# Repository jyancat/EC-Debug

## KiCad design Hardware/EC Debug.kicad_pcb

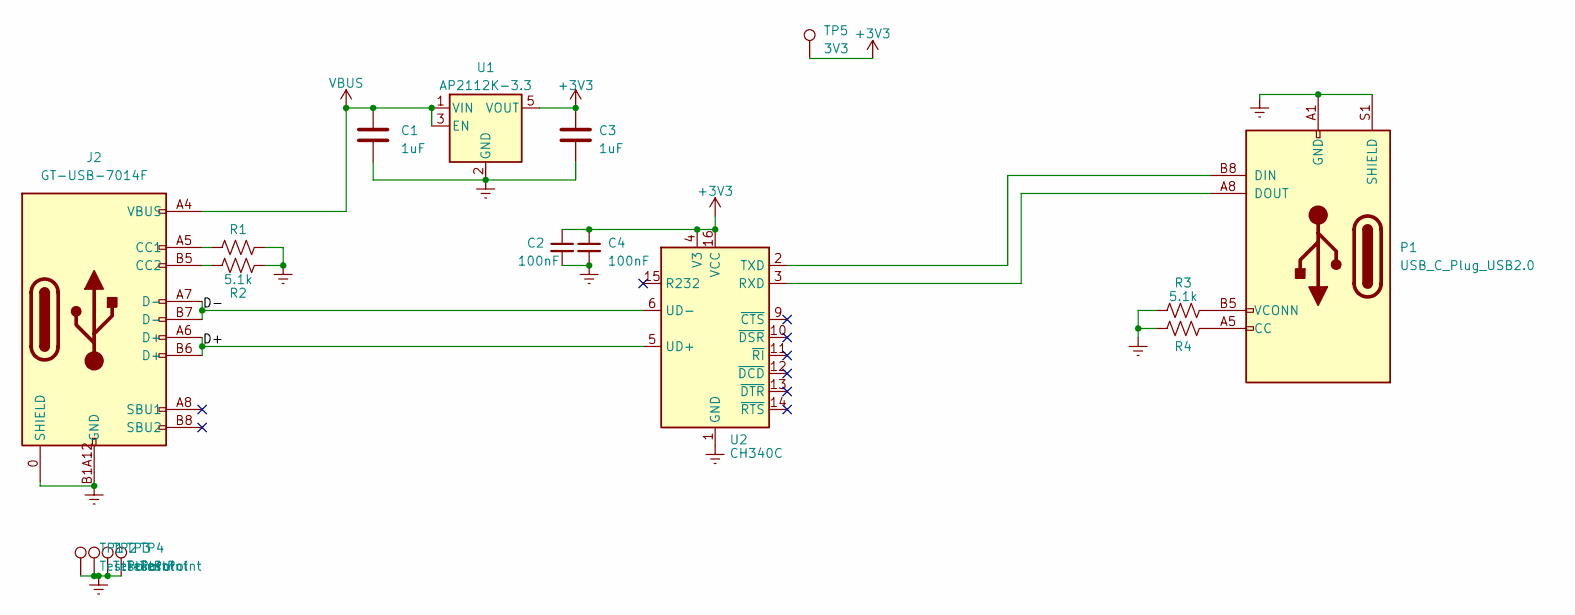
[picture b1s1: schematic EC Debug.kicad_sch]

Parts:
C1, C3: 1uF; C_0402_1005Metric
C2, C4: 100nF; C_0402_1005Metric
J2: GT-USB-7014F; LCSC Part C3001282
P1: USB_C_Plug_USB2.0; 105444
R1, R2, R3, R4: 5.1k; R_0402_1005Metric
TP1, TP2, TP3, TP4: TestPoint; TestPoint_Pad_1.5x1.5mm
TP5: 3V3; TestPoint_Pad_D1.0mm
U1: AP2112K-3.3; SOT-23-5
U2: CH340C; SOIC-16_3.9x9.9mm_P1.27mm

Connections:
+3V3: C2.1, C3.1, C4.1, TP5.1, U1.5 (VOUT), U2.4 (V3), U2.16 (VCC)
/D+: J2.A6 (D+), J2.B6 (D+), U2.5 (UD+)
/D-: J2.A7 (D-), J2.B7 (D-), U2.6 (UD-)
Earth: C1.2, C2.2, C3.2, C4.2, J2.0 (SHIELD), J2.A1B12 (GND), J2.B1A12 (GND), P1.A1 (GND), P1.A12 (GND), P1.B1 (GND), P1.B12 (GND), P1.S1 (SHIELD), R1.1, R2.1, R3.1, R4.1, TP1.1, TP2.1, TP3.1, TP4.1, U1.2 (GND), U2.1 (GND)
unnamed: J2.A5 (CC1), R1.2
unnamed: J2.B5 (CC2), R2.2
unnamed: P1.A5 (CC), R4.2
unnamed: P1.B8 (DIN), U2.2 (TXD)
unnamed: P1.A8 (DOUT), U2.3 (RXD)
unnamed: P1.B5 (VCONN), R3.2
VBUS: C1.1, J2.A4 (VBUS), J2.B4 (VBUS), U1.1 (VIN), U1.3 (EN)

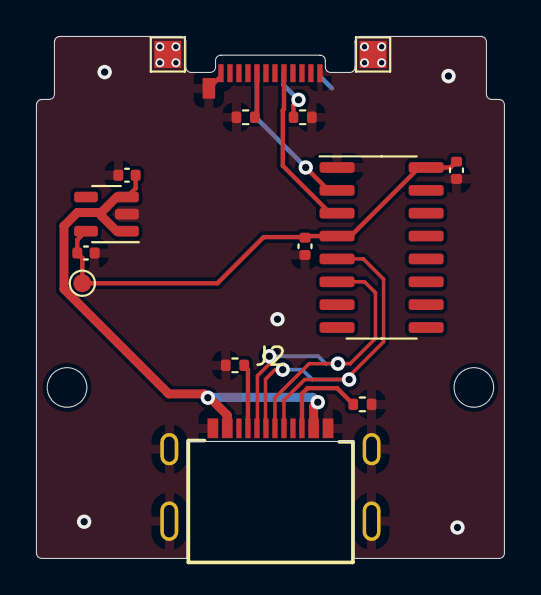
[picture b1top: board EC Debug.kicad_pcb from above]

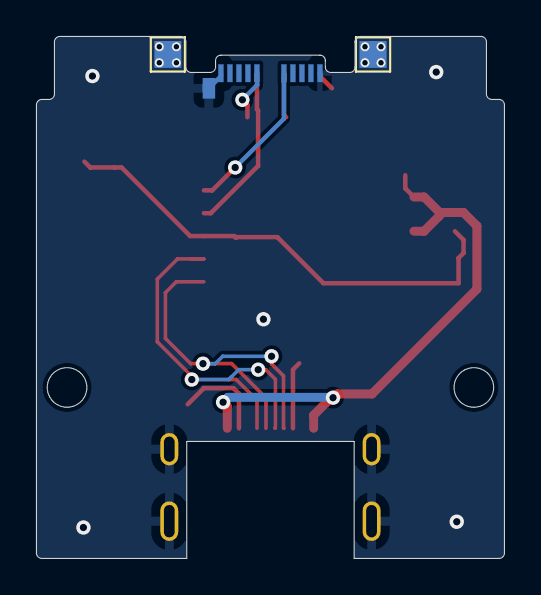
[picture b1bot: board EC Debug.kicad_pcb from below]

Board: 2 copper layers, 26.0 x 29.0 mm, 19 parts (2 on the bottom side), 11 nets.

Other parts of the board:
H1, H2: MountingHole; MountingHole_2.2mm_M2

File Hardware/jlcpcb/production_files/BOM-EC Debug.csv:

Comment,Designator,Footprint,LCSC
100nF,"C2,C4",C_0402_1005Metric,C100072
5.1k,"R1,R2,R3,R4",R_0402_1005Metric,C25905
GT-USB-7014F,J2,GT-USB-7014F,C3001282
AP2112K-3.3,U1,SOT-23-5,C427602
1uF,"C1,C3",C_0402_1005Metric,C52923
USB_C_Plug_USB2.0,P1,105444,C561769
CH340C,U2,SOIC-16_3.9x9.9mm_P1.27mm,C7464026

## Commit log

2024-08-14 Create LICENCE
